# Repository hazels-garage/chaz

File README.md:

# Chaz

Low Profile, Choc Spaced QAZ-alike

## Features
* QAZ Layout
* Choc Spaced
* Integrated STM32F702 microcontroller
* [Open Source](/source)

## Materials
* 1x Chaz PCB & Switchplate - [Buy](https://shop.hazel.cc/products/chaz-v03) - [Source](/source)
* 2x 2U Kailh Choc Stabalizers
* 37x Kailh Choc v1 Switches
* 37x Keycaps
  * 31x 1u 
  * 2x 1.25u
  * 1x 1.75u
  * 1x 1.5u
  * 1x 2u
  * 1x 2.25u
* 1x [Case](case/)
* 6x M2x6 countersunk screws  

## Build Steps
* Insert switches into switchplate
  * **NOTE**: There are 3 switches rotated differently from the rest.  Check the PCB to make sure you've got the correct orientation
* [Insert stabalizers](https://docs.keeb.io/choc-stabs)
* Place switchplate with switches onto PCB and press all the switches into their homes.
* Solder Switches
* Insert into case
* Screw Case to PCB from the bottom

## Firmware
To get into DFU, hold the DFU button on the bottom of the PCB while plugging in USB.

* [QMK](https://github.com/hazels-garage/qmk_firmware/tree/hazel/chaz)
* [VIAL](firmware/hazel_chaz_v03_vial.bin)
* [ZMK](https://github.com/hazels-garage/zmk-chaz)

## Changelog
* v0.3 - Current STM32F072CBT6 
* v0.2 - Unreleased and Unverified RP2040 
* v0.1 - Previously released ProMicro 
* v0.0 - Unreleased, but Verified ProMicro 

## Credits
* tominabox1 and whydobearsxplod for the original QAZ
* sporkus for [Le Chiffre STM32](https://github.com/sporkus/le_chiffre_keyboard_stm32) that I used as reference.
* [Pete Johanson](https://github.com/petejohanson) for suggesting I try STM32F072CBT6

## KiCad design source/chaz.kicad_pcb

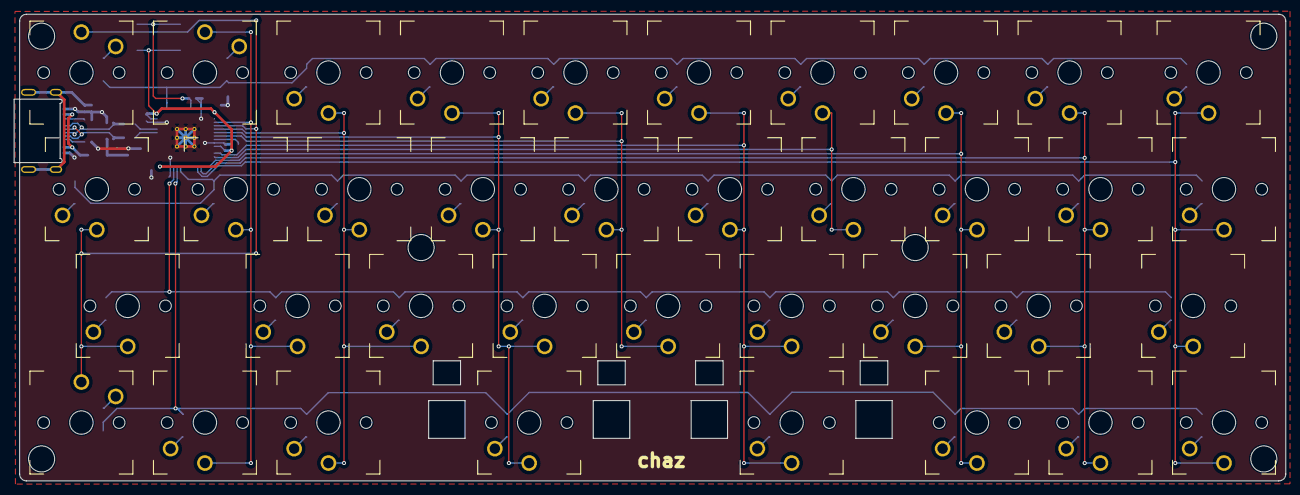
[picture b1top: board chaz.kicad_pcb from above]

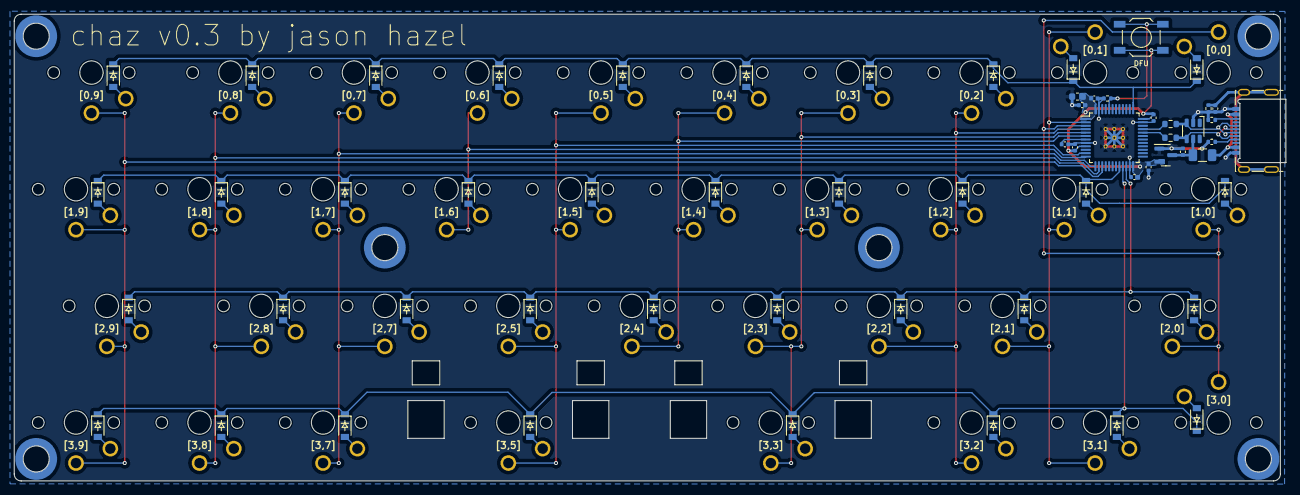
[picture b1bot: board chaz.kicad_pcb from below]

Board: 2 copper layers, 185.3 x 68.0 mm, 102 parts (65 on the bottom side), 64 nets.

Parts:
BOOT0: DFU; SW_SPST_TL3342
C1, C2: 1uF; C_0402_1005Metric
C3, C4, C5, C6, C7, C9: 100nF; C_0402_1005Metric
C8: 10uF; C_0603_1608Metric
C_Shield1: 4.7n; C_0402_1005Metric
D1, D2, D3, D4, D5, D6, D7, D8, D9, D10, D11, D12, D13, D14, D15, D16, D17, D18, D19, D20, D21, D22, D23, D24, D25, D26, D27, D28, D29, D30, D31, D32, D33, D34, D35, D36, D37: 1N4148W; D_SOD-123
F1: 500mA; Fuse_1206_3216Metric
H1, H2, H3, H4, H5, H6: MountingHole; MountingHole_M2_Pad_NonPTH_TopOnly
J1: USB_C; Molex-216990_GCT-USB45xx_HRO-TYPE-C-31-M-13x
R1, R2: 5.1k; R_0402_1005Metric
R3, R4: 27R; R_0603_1608Metric
R5: 10k; R_0402_1005Metric
R_Shield1: 1M; R_0402_1005Metric
SW1: [3,0]; choc-1u-millmax
SW2: [3,1]; choc-1u-millmax
SW3: [3,2]; choc-1u-millmax
SW4: [3,3]; Choc-2.25u-millmax
SW5: [3,5]; Choc-2u-millmax
SW6: [3,7]; choc-1u-millmax
SW7: [3,8]; choc-1u-millmax
SW8: [3,9]; choc-1u-millmax
SW9: [2,0]; Choc-1.75u-millmax
SW10: [2,1]; choc-1u-millmax
SW11: [2,2]; choc-1u-millmax
SW12: [2,3]; choc-1u-millmax
SW13: [2,4]; choc-1u-millmax
SW14: [2,5]; choc-1u-millmax
SW15: [2,7]; choc-1u-millmax
SW16: [2,8]; choc-1u-millmax
SW17: [2,9]; Choc-1.5u-millmax
SW18: [1,0]; Choc-1.25u-millmax
SW19: [1,1]; choc-1u-millmax
SW20: [1,2]; choc-1u-millmax
SW21: [1,3]; choc-1u-millmax
SW22: [1,4]; choc-1u-millmax
SW23: [1,5]; choc-1u-millmax
SW24: [1,6]; choc-1u-millmax
SW25: [1,7]; choc-1u-millmax
SW26: [1,8]; choc-1u-millmax
SW27: [1,9]; choc-1u-millmax
SW28: [0,0]; choc-1u-millmax
SW29: [0,1]; choc-1u-millmax
SW30: [0,2]; choc-1u-millmax
SW31: [0,3]; choc-1u-millmax
SW32: [0,4]; choc-1u-millmax
SW33: [0,5]; choc-1u-millmax
SW34: [0,6]; choc-1u-millmax
SW35: [0,7]; choc-1u-millmax
SW36: [0,8]; choc-1u-millmax
SW37: [0,9]; Choc-1.25u-millmax
U1: STM32F072CBT6; LQFP-48_7x7mm_P0.5mm
U2: SRV05-4; SOT-23-6-routable
U3: XC6206; SOT-23

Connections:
+3V3: BOOT0.1, C2.2, C3.1, C4.1, C5.1, C6.1, C7.1, C8.1, U1.1 (VBAT), U1.9 (VDDA), U1.24 (VDD), U1.36 (VDDIO2), U1.48 (VDD), U3.2 (VO)
+5V: C1.2, F1.2, U2.5 (VP), U3.3 (VI)
/stm32f072c/CC1: J1.A5 (CC1), R1.1
/stm32f072c/CC2: J1.B5 (CC2), R2.1
A1: SW5.2, SW14.2, SW23.2, SW33.2, U1.11 (PA1)
A2: SW24.2, SW34.2, U1.12 (PA2)
A3: SW6.2, SW15.2, SW25.2, SW35.2, U1.13 (PA3)
A4: SW7.2, SW16.2, SW26.2, SW36.2, U1.14 (PA4)
A5: SW8.2, SW17.2, SW27.2, SW37.2, U1.15 (PA5)
A14: D28.1 (K), D29.1 (K), D30.1 (K), D31.1 (K), D32.1 (K), D33.1 (K), D34.1 (K), D35.1 (K), D36.1 (K), D37.1 (K), U1.37 (PA14)
B2: D18.1 (K), D19.1 (K), D20.1 (K), D21.1 (K), D22.1 (K), D23.1 (K), D24.1 (K), D25.1 (K), D26.1 (K), D27.1 (K), U1.20 (PB2)
B10: D1.1 (K), D2.1 (K), D3.1 (K), D4.1 (K), D5.1 (K), D6.1 (K), D7.1 (K), D8.1 (K), U1.21 (PB10)
B11: D9.1 (K), D10.1 (K), D11.1 (K), D12.1 (K), D13.1 (K), D14.1 (K), D15.1 (K), D16.1 (K), D17.1 (K), U1.22 (PB11)
BOOT0: BOOT0.2, R5.1, U1.44 (BOOT0)
C13: SW2.2, SW10.2, SW19.2, SW29.2, U1.2 (PC13)
C14: SW1.2, SW9.2, SW18.2, SW28.2, U1.3 (PC14)
C15: SW3.2, SW11.2, SW20.2, SW30.2, U1.4 (PC15)
DBUS+: J1.A6 (D+), J1.B6 (D+), R3.1, U2.3 (IO2)
DBUS-: J1.A7 (D-), J1.B7 (D-), R4.1, U2.4 (IO3)
F0: SW4.2, SW12.2, SW21.2, SW31.2, U1.5 (PF0)
F1: SW13.2, SW22.2, SW32.2, U1.6 (PF1)
GND: C1.1, C2.1, C3.2, C4.2, C5.2, C6.2, C7.2, C8.2, C9.2, C_Shield1.1, J1.A1 (GND), J1.A12 (GND), J1.B1 (GND), J1.B12 (GND), R1.2, R2.2, R5.2, R_Shield1.2, U1.8 (VSSA), U1.23 (VSS), U1.35 (VSS), U1.47 (VSS), U2.2 (VN), U3.1 (GND)
GNDREF: C_Shield1.2, J1.S1 (SHIELD), R_Shield1.1
NRST: C9.1, U1.7 (NRST)
unnamed: D1.2 (A), SW1.1
unnamed: D2.2 (A), SW2.1
unnamed: D3.2 (A), SW3.1
unnamed: D4.2 (A), SW4.1
unnamed: D5.2 (A), SW5.1
unnamed: D6.2 (A), SW6.1
unnamed: D7.2 (A), SW7.1
unnamed: D8.2 (A), SW8.1
unnamed: D9.2 (A), SW9.1
unnamed: D10.2 (A), SW10.1
unnamed: D11.2 (A), SW11.1
unnamed: D12.2 (A), SW12.1
unnamed: D13.2 (A), SW13.1
unnamed: D14.2 (A), SW14.1
unnamed: D15.2 (A), SW15.1
unnamed: D16.2 (A), SW16.1
unnamed: D17.2 (A), SW17.1
unnamed: D18.2 (A), SW18.1
unnamed: D19.2 (A), SW19.1
unnamed: D20.2 (A), SW20.1
unnamed: D21.2 (A), SW21.1
unnamed: D22.2 (A), SW22.1
unnamed: D23.2 (A), SW23.1
unnamed: D24.2 (A), SW24.1
unnamed: D25.2 (A), SW25.1
unnamed: D26.2 (A), SW26.1
unnamed: D27.2 (A), SW27.1
unnamed: D28.2 (A), SW28.1
unnamed: D29.2 (A), SW29.1
unnamed: D30.2 (A), SW30.1
unnamed: D31.2 (A), SW31.1
unnamed: D32.2 (A), SW32.1
unnamed: D33.2 (A), SW33.1
unnamed: D34.2 (A), SW34.1
unnamed: D35.2 (A), SW35.1
unnamed: D36.2 (A), SW36.1
unnamed: D37.2 (A), SW37.1
unnamed: R4.2, U1.32 (PA11)
unnamed: R3.2, U1.33 (PA12)
VBUS: F1.1, J1.A4 (VBUS), J1.A9 (VBUS), J1.B4 (VBUS), J1.B9 (VBUS)

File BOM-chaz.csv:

Comment,Designator,Footprint,LCSC
DFU,BOOT0,SW_SPST_TL3342,C115351
4.7n,C_Shield1,C_0402_1005Metric,C1538
10uF,C8,C_0603_1608Metric,C19702
USB_C,J1,Molex-216990_GCT-USB45xx_HRO-TYPE-C-31-M-13x,C223906
27R,"R3,R4",R_0603_1608Metric,C25190
10k,R5,R_0402_1005Metric,C25744
5.1k,"R1,R2",R_0402_1005Metric,C25905
1M,R_Shield1,R_0402_1005Metric,C26083
MountingHole,"H1,H2,H3,H4,H5,H6",MountingHole_M2_Pad_NonPTH_TopOnly,C2916384
100nF,"C3,C4,C5,C6,C7,C9",C_0402_1005Metric,C307331
1uF,"C1,C2",C_0402_1005Metric,C52923
XC6206,U3,SOT-23,C5446
500mA,F1,Fuse_1206_3216Metric,C70076
1N4148W,"D1,D10,D11,D12,D13,D14,D15,D16,D17,D18,D19,D2,D20,D21,D22,D23,D24,D25,D26,D27,D28,D29,D3,D30,D31,D32,D33,D34,D35,D36,D37,D4,D5,D6,D7,D8,D9",D_SOD-123,C81598
STM32F072CBT6,U1,LQFP-48_7x7mm_P0.5mm,C81720
SRV05-4,U2,SOT-23-6-routable,C85364

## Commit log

2023-05-29 init chaz
2023-05-29 remove incorrect link
2023-05-30 fix formatting
2023-05-30 fixing copy/paste misses
2023-06-11 adding vial firmwares
2023-07-05 add sponsor info
2023-07-14 test
2023-09-01 Update FIRMWARE.md
    adding link to ZMK Config
2023-12-14 adding v0.3
2023-12-14 picture
2023-12-15 update zmk links
2023-12-27 adding source
2023-12-27 add license
2023-12-30 fixed small gap in case that was causing printing artifacts
2025-02-21 remove NC from license.
2026-03-26 Remove Hazel's Garage badge from README
    Removed Hazel's Garage badge from README.

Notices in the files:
README.md:
https://img.shields.io/badge/CC--BY--SA-test?style=flat-square&logo=creativecommons&logoColor=ffffff&label=%20&labelColor=8CBA04&color=8CBA04
